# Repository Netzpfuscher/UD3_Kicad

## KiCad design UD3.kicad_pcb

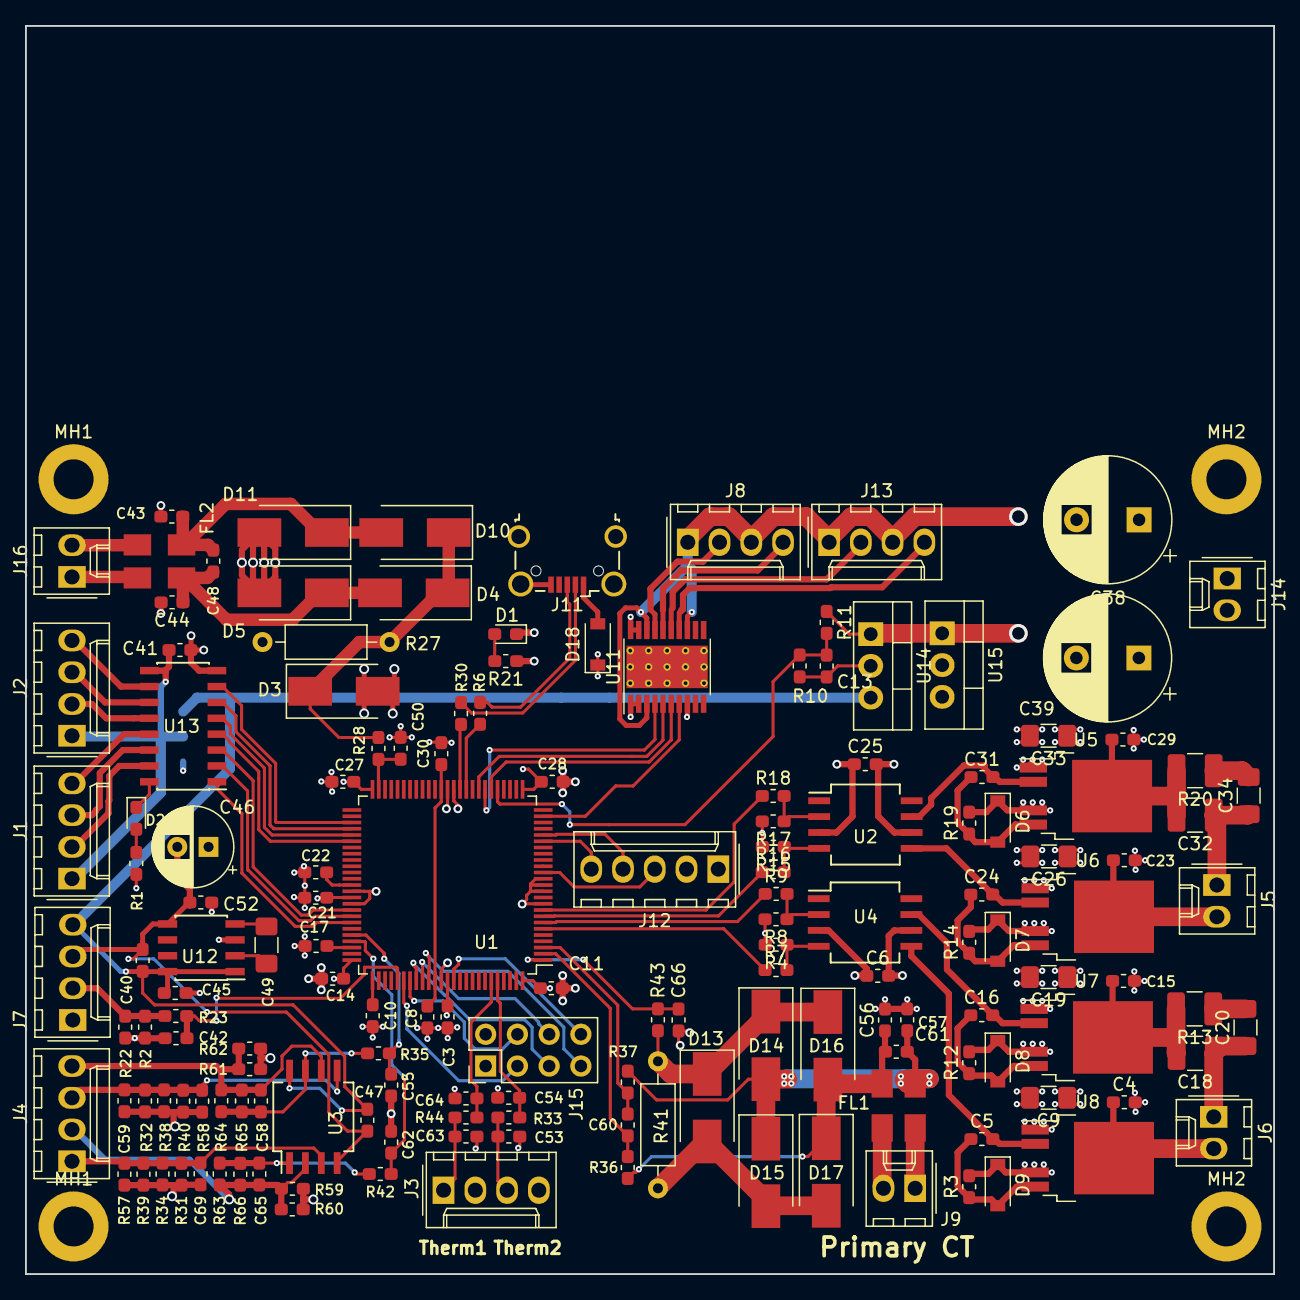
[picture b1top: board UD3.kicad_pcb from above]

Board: 4 copper layers, 99.8 x 99.8 mm, 160 parts (1 on the bottom side), 103 nets.

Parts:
C3, C8, C10, C11, C21, C22, C27, C28, C30, C40, C41, C45, C47, C52: 1µF; C_0603_1608Metric_Pad1.05x0.95mm_HandSolder
C4, C15, C23, C29, C42, C48, C61: 1nF; C_0603_1608Metric_Pad1.05x0.95mm_HandSolder
C5, C13, C14, C16, C17, C24, C31, C53, C54, C63, C64: 100nF; C_0603_1608Metric_Pad1.05x0.95mm_HandSolder
C6, C25: 1µ; C_0603_1608Metric_Pad1.05x0.95mm_HandSolder
C9, C19, C26, C33, C49: 4µ7; C_1206_3216Metric_Pad1.42x1.75mm_HandSolder
C18, C32: 2µ2; C_1210_3225Metric_Pad1.42x2.65mm_HandSolder
C20, C34: 1µ; C_1206_3216Metric_Pad1.42x1.75mm_HandSolder
C38, C39: CP; CP_Radial_D10.0mm_P5.00mm
C43, C44, C50, C56, C57, C60, C66: 150pF; C_0603_1608Metric_Pad1.05x0.95mm_HandSolder
C46: 100µF; CP_Radial_D6.3mm_P2.50mm
C55, C58, C59, C62, C65, C69: 10nF; C_0603_1608Metric_Pad1.05x0.95mm_HandSolder
D1: PWR; LED_0603_1608Metric_Pad1.05x0.95mm_HandSolder
D2: LED1; LED_0603_1608Metric_Pad1.05x0.95mm_HandSolder
D3, D13: SMBJ5.0CA; D_SMB_Handsoldering
D4, D5, D10, D11, D14, D15, D16, D17: E2D; D_SMB_Handsoldering
D6, D7, D8, D9: 1N4148W; D_SOD-123
D18: MBR0530; D_SOD-123
FL1, FL2: DLW5BTM501SQ2L; 2020
J1: LED_CON2; Molex_KK-254_AE-6410-04A_1x04_P2.54mm_Vertical
J2: LED_CON1; Molex_KK-254_AE-6410-04A_1x04_P2.54mm_Vertical
J3: THERM; Molex_KK-254_AE-6410-04A_1x04_P2.54mm_Vertical
J4: UMEAS; Molex_KK-254_AE-6410-04A_1x04_P2.54mm_Vertical
J5, J14: GDT2; Molex_KK-254_AE-6410-02A_1x02_P2.54mm_Vertical
J6: GDT1; Molex_KK-254_AE-6410-02A_1x02_P2.54mm_Vertical
J7: IBUS; Molex_KK-254_AE-6410-04A_1x04_P2.54mm_Vertical
J8, J13: RLY; Molex_KK-254_AE-6410-04A_1x04_P2.54mm_Vertical
J9, J16: CT; Molex_KK-254_AE-6410-02A_1x02_P2.54mm_Vertical
J11: USB_B_Micro; USB_Micro-B_Wuerth_629105150521_CircularHoles
J12: Prog; Molex_KK-254_AE-6410-05A_1x05_P2.54mm_Vertical
J15: Conn_02x04_Odd_Even; PinHeader_2x04_P2.54mm_Vertical
JP1: Jumper_NC_Dual; SolderJumper-3_P2.0mm_Open_TrianglePad1.0x1.5mm
MH1, MH1#2, MH2, MH2#2: MountingHole_Pad; MountingHole_3.2mm_M3_DIN965_Pad
R1, R21, R23: 470; R_0603_1608Metric_Pad1.05x0.95mm_HandSolder
R2, R22, R33, R36, R37, R44: 100; R_0603_1608Metric_Pad1.05x0.95mm_HandSolder
R3, R7, R9, R12, R14, R16, R18, R19, R28, R35, R42, R43: 1k; R_0603_1608Metric_Pad1.05x0.95mm_HandSolder
R4, R8, R10, R11, R15, R17, R31, R32, R34, R38, R39, R40, R57, R58, R59, R60, R61, R62, R63, R64, R65, R66: 10k; R_0603_1608Metric_Pad1.05x0.95mm_HandSolder
R6, R30: 22; R_0603_1608Metric_Pad1.05x0.95mm_HandSolder
R13, R20: 15; R_1210_3225Metric_Pad1.42x2.65mm_HandSolder
R27, R41: 3,3; R_Axial_DIN0207_L6.3mm_D2.5mm_P10.16mm_Horizontal
U1: CY8C5868AXI-LP035; TQFP-100_14x14mm_P0.5mm
U2, U4: MIC4426; SO-8_5.3x6.2mm_P1.27mm
U3: TL082; SO-8_5.3x6.2mm_P1.27mm
U5, U6, U7, U8: DMC3021LK4; TO-252-4
U11: IPS4260L; HTSSOP-20-1EP_4.4x6.5mm_P0.65mm_EP3.4x6.5mm_ThermalVias
U12: TC7662Bx0A; SOIC-8_3.9x4.9mm_P1.27mm
U13: ULN2003LV; SOIC-16_3.9x9.9mm_P1.27mm
U14: LM7812_TO220; TO-220-3_Vertical
U15: LM7805_TO220; TO-220-3_Vertical

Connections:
+5C: C3.2, C6.2, C11.1, C14.2, C21.2, C25.2, C27.1, C28.1, D18.1, J12.1, J15.1, JP1.3, R1.1, R21.1, U1.26, U1.37, U1.50, U1.65, U1.75, U1.88, U1.100, U2.6, U4.6, U15.3
+12V: C40.1, C45.1, C47.2, J7.4, JP1.1, U3.8, U12.1, U12.8, U14.3
+24V: C9.1, C19.1, C26.1, C33.1, C38.1, C39.1, D6.1, D7.1, D8.1, D9.1, J8.1, J8.3, J13.1, J13.3, J14.1, R3.2, R11.1, R12.2, R14.2, R19.2, U5.4, U6.4, U7.4, U8.4, U11.3, U11.13, U11.18, U14.1, U15.1
-12V: C40.2, C46.2, C47.1, C52.1, J7.3, U3.4, U12.5
Dn: R30.1, U1.36
Dp: R6.1, U1.35
FAN: U1.31, U11.6
GD1A: R9.1, U1.7
GD1B: R7.1, U1.6
GD2A: R18.1, U1.9
GD2B: R16.1, U1.8
GND: C3.1, C4.2, C6.1, C8.1, C9.2, C10.2, C11.2, C13.2, C14.1, C15.2, C17.2, C19.2, C21.1, C22.2, C23.2, C25.1, C26.2, C27.2, C28.2, C29.2, C30.2, C33.2, C38.2, C39.2, C41.2, C42.2, C43.2, C44.2, C45.2, C46.1, C50.2, C52.2, C53.2, C54.2, C55.2, C56.2, C57.2, C59.2, C62.2, C63.2, C64.2, C66.2, C69.2, D1.1, D3.2, D5.2, D11.2, D13.2, D15.2, D17.2, J3.2, J3.4, J7.1, J11.5, J11.6, J12.2, J14.2, J15.2, MH1.1, MH1#2.1, MH2.1, MH2#2.1, R2.2, R4.2, R8.2, R10.2, R15.2, R17.2, R22.2, R27.1, R31.1, R32.1, R34.1, R38.1, R39.1, R40.1, R41.1, R57.1, R58.1, R59.2, R60.2, R61.2, R62.2, U1.10, U1.12, U1.13, U1.14, U1.38, U1.64, U1.66, U1.87, U2.3, U4.3, U5.1, U6.1, U7.1, U8.1, U11.1, U11.2, U11.8, U11.19, U11.20, U12.3, U13.8, U14.2, U15.2
GPIO_4_3: J15.3, U1.81
GPIO_4_4: J15.4, U1.82
GPIO_4_5: J15.5, U1.83
GPIO_4_6: J15.6, U1.84
GPIO_4_7: J15.7, U1.85
GPIO_6_0: J15.8, U1.89
IBUS: C42.1, R23.1, U1.80
Iprim: C66.1, R43.1, U1.1
Isec: C50.1, R28.1, U1.49
LED1: U1.69, U13.1
LED2: U1.68, U13.2
LED3: U1.67, U13.3
LED4: U1.56, U13.4
LED5: U1.55, U13.5
LED6: U1.54, U13.6
LED7: U1.53, U13.7
unnamed: C4.1, J6.2, U8.3
unnamed: C5.1, D9.2, R3.1, U8.5
unnamed: C5.2, U4.5, U8.2
unnamed: C10.1, U1.76
unnamed: C15.1, C18.2, R13.2, U7.3
unnamed: C16.1, D8.2, R12.1, U7.5
unnamed: C16.2, U4.7, U7.2
unnamed: C17.1, U1.73
unnamed: C18.1, C20.1, J6.1
unnamed: C20.2, R13.1
unnamed: C22.1, U1.63
unnamed: C23.1, J5.2, U6.3
unnamed: C24.1, D7.2, R14.1, U6.5
unnamed: C24.2, U2.5, U6.2
unnamed: C29.1, C32.2, R20.2, U5.3
unnamed: C8.2, C30.1, U1.39, U1.86
unnamed: C31.1, D6.2, R19.1, U5.5
unnamed: C31.2, U2.7, U5.2
unnamed: C32.1, C34.1, J5.1
unnamed: C34.2, R20.1
unnamed: C41.1, J1.1, J2.1, JP1.2, U13.9
unnamed: C43.1, C48.2, D10.2, D11.1, FL2.4
unnamed: C44.1, C48.1, D4.2, D5.1, FL2.2
unnamed: C49.1, U12.2
unnamed: C49.2, U12.4
unnamed: C53.1, J3.3, R33.2
unnamed: C56.1, C61.2, D16.2, D17.1, FL1.4, R36.2
unnamed: C57.1, C61.1, D14.2, D15.1, FL1.2, R37.2
unnamed: C58.1, R35.2, R64.1, R65.1, U3.7
unnamed: C58.2, J4.4, R61.1, R62.1, R64.2, R65.2, U3.6
unnamed: C59.1, J4.3, R32.2, R38.2, R40.2, R58.2, U3.5
unnamed: C63.1, J3.1, R44.2
unnamed: C65.1, R42.2, R63.1, R66.1, U3.1
unnamed: C65.2, J4.2, R59.1, R60.1, R63.2, R66.2, U3.2
unnamed: C69.1, J4.1, R31.2, R34.2, R39.2, R57.2, U3.3
unnamed: D1.2, R21.2
unnamed: D2.1, U13.16
unnamed: D2.2, R1.2
unnamed: D3.1, D4.1, D10.1, R27.2, R28.2
unnamed: D13.1, D14.1, D16.1, R41.2, R43.2
unnamed: D18.2, J11.1
unnamed: FL1.1, J9.1
unnamed: FL1.3, J9.2
unnamed: FL2.1, J16.1
unnamed: FL2.3, J16.2
unnamed: J1.2, U13.15
unnamed: J1.3, U13.14
unnamed: J1.4, U13.13
unnamed: J2.2, U13.12
unnamed: J2.3, U13.11
unnamed: J2.4, U13.10
unnamed: J7.2, R2.1, R22.1, R23.2
unnamed: J8.2, U11.17
unnamed: J8.4, U11.16
unnamed: J11.2, R30.2
unnamed: J11.3, R6.2
unnamed: J13.2, U11.15
unnamed: J13.4, U11.14
unnamed: R4.1, R7.2, U4.4
unnamed: R8.1, R9.2, U4.2
unnamed: R15.1, R16.2, U2.4
unnamed: R17.1, R18.2, U2.2
RST: J12.3, U1.15
Relay1: U1.32, U11.4
Relay2: U1.33, U11.5
Relay3: U1.24, U11.7
SWDCLK: J12.4, U1.21
SWDIO: J12.5, U1.20
UVLO: C13.1, R10.1, R11.2, U1.30
Vbus: C55.1, R35.1, U1.71
Vin: C62.1, R42.1, U1.72
ZCDA: C60.1, R37.1, U1.3
ZCDB: C60.2, R36.1, U1.2
therm1: C64.1, R44.1, U1.95
therm2: C54.1, R33.1, U1.96

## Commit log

2019-10-23 Removed W5500
